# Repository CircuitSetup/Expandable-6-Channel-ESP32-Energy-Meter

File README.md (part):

# CircuitSetup Expandable 6 Channel ESP32 Energy Meter

The CircuitSetup Expandable 6 Channel ESP32 Energy Meter is a real-time power and energy monitor built around two ATM90E32AS metering ICs. The main board measures six current transformer channels and one voltage reference by default, and you can stack up to six add-on boards for a total of 42 current channels. It is a good fit for whole-home monitoring, subpanels, solar, large branch circuits, and multi-voltage or 3-phase projects.

The first AC-AC adapter powers the main board and provides the primary voltage reference. A second voltage can be measured on the main board, and stacked systems can monitor additional voltage references when the hardware is configured for it.

## Table of Contents

- [Quick Start: ESPHome via ESP Web Installer](#quick-start-esphome-via-esp-web-installer)
- [What You Will Need](#what-you-will-need)
- [Setting Up the Meter](#setting-up-the-meter)
- [Software Options](#software-options)
- [FAQ](#faq)
- [More Resources](#more-resources)

## Typical Uses

- North American split-phase 120V/240V 60Hz service: mains, solar, subpanels, and individual circuits
- Single-phase 230V/240V 50Hz or 60Hz systems with a suitable 9VAC or 12VAC AC-AC adapter
- 3-phase systems when each measured phase has the correct voltage reference

## Features

- 6 current channels on the main board
- Expandable to 42 current channels and up to 8 voltage references with add-on boards
- Built around two ATM90E32AS energy metering ICs
- Calculates active power, reactive power, apparent power, power factor, frequency, and temperature
- 16-bit measurement resolution
- 22 ohm burden resistors on each current channel
- Built-in buck converter to power the board and supported ESP32 dev boards
- SPI interface to the ESP32
- Energy pulse outputs, IRQ outputs, warning output, and zero-crossing signals are available on the board
- Typical metering IC accuracy is 0.1 percent with a 6000:1 dynamic range
- Current gain selection is available up to 4x

## Quick Start: ESPHome via ESP Web Installer

The fastest way to get the meter running is to flash ESPHome directly from the [CircuitSetup ESP Web Installer](https://circuitsetup.github.io/ESPWebInstaller/), connect it to your network, then adopt the device into Home Assistant.

### Flash Now With the Web Installer

1. Open the [CircuitSetup ESP Web Installer](https://circuitsetup.github.io/ESPWebInstaller/)
2. Under `6 Channel Meter`, choose:
   - the number of add-on boards
   - the connection type: `Wi-Fi`, `Ethernet (Lilygo)`, or `Ethernet (Waveshare)`
3. Choose the firmware version
4. Connect the ESP32 to your computer with a USB data cable
5. Click `Connect`, choose the correct serial port, and start the flash
6. If the board does not enter the bootloader automatically, hold the right or `IO0` button while the installer starts
7. If you flashed a Wi-Fi build, provision Wi-Fi after the flash
8. Once the device is online, adjust names, calibration values, and extra sensors as needed

The current Wi-Fi configs in this repo already include `captive_portal`, `esp32_improv`, and `improv_serial`, so the device can be provisioned before it is ever adopted into Home Assistant.

### Adopt Into Home Assistant/ESPHome Device Builder

If you want UI-based management, dashboard imports, OTA updates from Home Assistant, to change default meter/CT names, and do any other YAML editing, install ESPHome Device Builder after the first flash.

1. Open `Settings > Add-ons > Add-on Store`
2. Search for `ESPHome Device Builder`
3. Install it, then click `Start`
4. Click `Open Web UI`

The device should then appear in ESPHome Device Builder and in Home Assistant under `Settings > Devices & services`.

For package layout, local copies, calibration files, CS-pin changes, and advanced YAML examples, see [Software/ESPHome/](Software/ESPHome/).

## What You Will Need

### Current Transformers

You can use any mix of supported CTs as long as the secondary output does not exceed 720mV RMS or 33mA. CircuitSetup CTs with mA output work directly with the board and do not require cutting the burden resistor jumpers on the back.

- [SCT-006 20A/25mA Micro CT](https://circuitsetup.us/product/20a-25ma-micro-current-transformer-yhdc-sct-006-6mm/) - 6mm opening, 3.5mm plug
- [SCT-010 80A/26.6mA Mini CT](https://circuitsetup.us/product/80a-26-6ma-mini-current-transformer-yhdc-sct-010-10mm/) - 10mm opening, 3.5mm plug
- [SCT-013-000 100A/50mA CT](https://circuitsetup.us/product/100a-50ma-current-transformer-yhdc-sct-013/) - 13mm opening, 3.5mm plug
- [SCT-016 120A/40mA CT](https://circuitsetup.us/product/120a-40ma-current-transformer-yhdc-sct-016-with-3-5mm-jack-16mm-opening/) - 16mm opening, 3.5mm plug
- [SCT-024 200A/50mA CT](https://circuitsetup.us/product/200a-50ma-current-transformer-yhdc-sct-024-24mm/) - 24mm opening, 3.5mm plug
- Magnelab SCT-0750-100 and similar voltage-output CTs can also be used, but channels using CTs with built-in burden resistors require the matching jumper trace on the back of the board to be cut

### AC-AC Transformer

The meter requires an AC output transformer, not a DC wall adapter.

- North America: [Jameco Reliapro 120V to 9VAC](https://circuitsetup.us/product/jameco-ac-to-ac-wall-adapter-transformer-9-volt-1000ma-black-straight-2-5mm-female-plug/) or a similar 9VAC or 12VAC adapter with a 2.5mm center pin
- Europe and other 230V regions: use a native 230V to 9VAC or 12VAC AC-AC adapter rated for at least 500mA. [OpenEnergyMonitor keeps a useful list here](https://learn.openenergymonitor.org/electricity-monitoring/voltage-sensing/different-acac-power-adapters)

### ESP32

Supported and documented controller options:

- [NodeMCU 32s](https://circuitsetup.us/product/nodemcu-32s-esp32-esp-wroom-32-development-board/)
- Espressif ESP32-DevKitC-32E
- Espressif ESP32-DevKitC-VIE
- Boards with the same 19-pin-per-side pinout as the boards above
- Ethernet options for ESPHome only: [CircuitSetup ESP32-S3 Ethernet Adapter](https://circuitsetup.us/product/6-channel-energy-meter-ethernet-adapter/), [LilyGO T-ETH-Lite ESP32-S3](https://www.lilygo.cc/products/t-eth-lite?variant=43120880779445), or [Waveshare ESP32-S3 ETH](https://www.waveshare.com/esp32-s3-eth.htm?sku=28972)

Boards with different pin maps are not drop-in compatible just because they are "ESP32" boards. For example, ESP32-C6 dev boards use different pins and are not part of the documented support path for this repo.
If you are comparing boards visually, the documented dev boards are usually 19 pins per side, with `3V3` at the upper-left corner and `CLK` at the lower-right corner when installed correctly.

### Software

- [ESPHome](https://esphome.io/components/sensor/atm90e32/) and [Home Assistant](https://www.home-assistant.io/integrations/esphome/) - recommended for most new installs
- [EmonESP](Software/EmonESP/readme.md) and [EmonCMS](https://emoncms.org/) - good if you want EmonCMS or MQTT without Home Assistant
- [CircuitPython library](https://github.com/BitKnitting/CircuitSetup_CircuitPython)
- [MicroPython library](https://github.com/BitKnitting/CircuitSetup_micropython)

## Setting Up the Meter

### Plugging In the ESP32

The board is designed so the ESP32 dev board plugs directly into the meter.

Always insert the ESP32 with `3V3` in the upper-left corner of the meter. The lower pins are used to pass the voltage reference to add-on boards. Plugging the ESP32 into the lower row will likely short the board.

### Main Board SPI and Chip-Select Pins

The meter communicates with the ESP32 over SPI.

Main board SPI pins:

- `CLK` - GPIO18
- `MISO` - GPIO19
- `MOSI` - GPIO23
- `CS1` - GPIO5 for CT1-CT3 and Voltage 1
- `CS2` - GPIO4 for CT4-CT6 and Voltage 2

The 6-channel version of EmonESP in this repo is already set up with the main board pin defaults. Current ESPHome configs for the main board and add-on boards are in [Software/ESPHome](Software/ESPHome).

### Add-On Boards

Each add-on board adds six more CT channels. Up to six add-on boards can be stacked on the main board.

Each add-on board has two CS jumper banks:

- `CS` for CT1-CT3 on that add-on board
- `CS2` for CT4-CT6 on that add-on board

Only choose one pin per bank. The default jumper positions used by the installer and repo configs are:

| Add-on board | `CS` for CT1-CT3 | `CS2` for CT4-CT6 |
| --- | --- | --- |
| 1st add-on | GPIO0 | GPIO16 |
| 2nd add-on | GPIO27 | GPIO17 |
| 3rd add-on | GPIO2 | GPIO21 |
| 4th add-on | GPIO13 | GPIO22 |
| 5th add-on | GPIO14 | GPIO25 |
| 6th add-on | GPIO15 | GPIO26 |

GPIO2 can interfere with programming on some ESP32 boards. If you temporarily cannot flash the ESP32 while that jumper is connected, disconnect that add-on board or move the jumper while programming, then restore the expected setting.

If you change jumper positions from the defaults, update the matching `cs_pin` values in your ESPHome config. See [Software/ESPHome/README.md](Software/ESPHome/README.md) for examples.

### CT Compatibility, Burden Resistors, and `JP1-JP6`

Each current channel on the board has an onboard burden resistor. That is correct for CircuitSetup CTs with mA output.

Only cut the matching rear jumper trace for a CT channel if that CT already has its own burden resistor, which is usually the case for voltage-output CTs such as 1V-output models.

In practice:

- CircuitSetup SCT-006, SCT-010, SCT-013-000, SCT-016, and SCT-024 CTs do not require cutting `JP1-JP6`
- 1V-output CTs such as SCT-013-030 or SCT-013-050 do require cutting the matching jumper trace for the channel they are connected to
- If you are mixing CT types, only cut the jumper traces for the specific channels using CTs with built-in burden resistors

### Common Calibration Starting Values

Each current channel can use its own calibration value. In the current ESPHome configs that means setting `current_cal_ct1`, `current_cal_ct2`, and so on for the main board, plus the add-on board calibration variables where needed.

Common starting values:

| Sensor | Calibration value |
| --- | --- |
| SCT-006 20A/25mA | `11143` |
| SCT-013-030 30A/1V | `8650` |
| SCT-013-050 50A/1V | `15420` |
| SCT-010 50A/16.6mA | `41334` |
| SCT-010 80A/26.6mA | `41660` |
| SCT-013-000 100A/50mA | `27518` |
| SCT-016 120A/40mA | `41787` |
| SCT-024 200A/100mA | `27518` |
| SCT-024 200A/50mA | `55036` |
| Jameco 9VAC transformer | `7305` |

These are good starting points, not guaranteed final values. If you want tighter accuracy, use the ESPHome semi-automatic calibration workflow described below.

### Measuring More Than 65A on One Channel

The ATM90E32 current register tops out at `65.535A` before scaling. If you expect to measure more than that on one channel, divide the CT calibration value and multiply the reported current and power in software. Current examples are already documented in [Software/ESPHome/README.md](Software/ESPHome/README.md) and shown in [Software/ESPHome/6chan_energy_meter_main_board.yaml](Software/ESPHome/6chan_energy_meter_main_board.yaml).

For 200A service this usually means you are monitoring a larger CT but scaling it in software so the meter stays within range.

### Power Calculations and Board Revisions

The board uses voltage references to calculate power, power factor, and the other metering values.

- v1.1 used one voltage channel per ATM90E32 by default, so some power calculations had to be done in software unless registers were remapped
- v1.2 and v1.3 added `JP8-JP11` so voltage channels could be tied together. Most v1.3 boards shipped with those connections already joined
- v1.4 and later removed `JP8-JP11` and route those voltage channels internally on the PCB

### Measuring Dual-Pole 240V Circuits on Split-Phase Service

For split-phase systems, a 240V load has two hot legs. There are three practical ways to measure it:

1. Measure one hot leg with one CT and double the current and power in software. This uses the fewest channels but is the least accurate.
2. Measure each hot leg with its own CT. This is the most flexible option.
3. If the wiring layout allows it and the CT opening is large enough, pass both hot legs through a single CT in opposite directions.

If a CT is not in phase with its voltage reference, current and power will read negative. On split-phase systems that usually means the CT is flipped around the wrong conductor.

### Measuring a Second Voltage

The `VA2` pads next to the power jack on the main board, and the `VA2` pads on add-on boards, let you measure a second voltage reference.

To do that:

1. Cut `JP12` and `JP13` on v1.3 and newer boards, or `JP7` on older revisions
2. Use a second AC-AC transformer, ideally the same model as the primary one
3. Connect that second transformer to the opposite phase you want to reference
4. Add a suitable connector or pigtail to the `VA2+` and `VA2-` pads

When those voltage jumpers are cut:

- CT1-CT3 stay referenced to the primary voltage
- CT4-CT6 use the `VA2` voltage reference

That means CT4-CT6 should measure circuits on the same phase as `VA2`, or the CT direction must be reversed so the current is in phase with the voltage reference.

On add-on boards, the primary voltage normally comes from the main board. If you wire a separate `VA2` voltage reference on an add-on board, that secondary voltage is used for CT4-CT6 on that add-on board.

### Measuring 3-Phase Power

For accurate 3-phase power metering you need a matching voltage reference for each measured phase.

The cleanest 3-phase setup is:

- one main board, v1.4 or newer
- one add-on board
- three AC-AC transformers, one per phase
- headers or connectors installed on the `VA2` pads as needed
- `JP12` and `JP13` cut on the boards where separate voltage references are being used

The first transformer connected to the main board also powers the electronics and ESP32, so it should provide at least 500mA.

With that hardware:

- main board CT1-CT3 can reference phase 1
- main board CT4-CT6 can reference phase 2
- add-on board CT1-CT6 can reference phase 3, depending on how you feed voltage to that board

An alternate 3-phase approach is to use two add-on boards and feed a separate transformer into each add-on board. In that setup, the bottom `VA-` and `VA+` feed from the main board is no longer used for those add-ons, and you wire the new transformer to the `VA2` pads on each add-on instead.

If a CT is tied to a different phase than its voltage reference, active power and power factor will be wrong even if current itself looks reasonable.

## Software Options

### ESPHome and Home Assistant

ESPHome is still the recommended software path. If you just want to get firmware onto the meter, use the quick-start section above. The rest of this section covers what the maintained ESPHome configs already include after the device is flashed.

Useful references:

- [Getting Started with ESPHome and Home Assistant](https://esphome.io/guides/getting_started_hassio/)
- [ESPHome ATM90E32 docs](https://esphome.io/components/sensor/atm90e32/)

### What the Default ESPHome Config Already Includes

The current repo configs are built for the current ESPHome workflow, not the older legacy setup:

- `dashboard_import` so the device can be adopted into ESPHome Device Builder
- `name_add_mac_suffix: true` so multiple identical meters do not collide on the network
- `ota: - platform: esphome` for current OTA updates
- `captive_portal`, `esp32_improv`, and `improv_serial` on Wi-Fi builds for provisioning
- `time: - platform: homeassistant` in the shared packages used by the standard configs

After the first flash:

- Wi-Fi builds can be provisioned from the browser, via Improv, or through the fallback captive portal if the device is not yet on your network
- Ethernet builds come up on your wired network once flashed and connected
- The device should appear in ESPHome Device Builder and in Home Assistant under `Settings > Devices & services`
- You can edit the imported YAML inside ESPHome Device Builder, or copy the files locally from [Software/ESPHome](Software/ESPHome) if you prefer to manage everything yourself

If you want the maintained package-based configs, start from the files in [Software/ESPHome](Software/ESPHome). If you want more control, use [Software/ESPHome/README.md](Software/ESPHome/README.md) as the advanced reference for package layout, calibration files, CS-pin changes, and example configs.

### ESPHome Calibration

Default calibration values are usually good enough to get started, but calibration is strongly recommended if you are using custom CTs, a different AC-AC transformer, longer CT leads, or if you want especially accurate readings.

On the main board, calibration is done through two separate ATM90E32 chips, not one 6-channel block. `main_meter_id1` / `Meter 1-3` handles CTs `1-3`, and `main_meter_id2` / `Meter 4-6` handles CTs `4-6`. Each `Run ... Calibration` button in Home Assistant acts on only one of those chips, so calibrate CTs `1-3` and CTs `4-6` separately.

In the CircuitSetup YAML, the normal starting points are `current_cal_ct1` through `current_cal_ct6`, plus `voltage_cal1` and `voltage_cal2` in the top-level config file you flashed or imported from [Software/ESPHome](Software/ESPHome). Under the hood, those map to ESPHome's `gain_ct` and `gain_voltage` values for each ATM90E32 phase. [Software/ESPHome/calibration/6chan_main_calibration.yaml](Software/ESPHome/calibration/6chan_main_calibration.yaml) adds the Home Assistant calibration buttons and the runtime reference number entities. [Software/ESPHome/calibration/6chan_main_offset_calibrations.yaml](Software/ESPHome/calibration/6chan_main_offset_calibrations.yaml) is where copied offset values can be persisted in YAML.

To use the semi-automatic calibration workflow, make sure `offset_calibration` and `gain_calibration` are set to `"true"` and that the calibration package is included. After the meter is adopted into Home Assistant, open the meter device page. There you will see:

- `${main_meter_name1} Ref V 1` and `CT1 Ref Current` through `CT3 Ref Current` for the first ATM90E32
- `${main_meter_name2} Ref V 2` and `CT4 Ref Current` through `CT6 Ref Current` for the second ATM90E32
- `Run ... Offset Cal`, `Run ... Power Offset Cal`, `Run ... Gain Cal`, and matching `Clear ...` buttons for each chip

If you renamed the meter groups in YAML, the button labels will follow those names instead of the default `Meter 1-3` and `Meter 4-6`.

In practice:

- gain calibration fixes scaling when the meter reads high or low under a known load
- offset calibration fixes false zero-level readings when current or voltage should be at or very near zero
- power-offset calibration fixes false power readings when voltage is present but CT current is zero

Recommended workflow:

1. Start with the closest known values for your CTs and AC transformer by setting `current_cal_ct1` through `current_cal_ct6` and `voltage_cal1`/`voltage_cal2` to the nearest matching starting values.
2. Open the meter device page in Home Assistant and choose which ATM90E32 you are calibrating: `Meter 1-3` for CTs `1-3`, or `Meter 4-6` for CTs `4-6`. For that chip, phase A/B/C in the ESPHome logs correspond to CT1/CT2/CT3 or CT4/CT5/CT6 respectively.
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
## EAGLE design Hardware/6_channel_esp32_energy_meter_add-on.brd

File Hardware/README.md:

## Expandable 6 Channel Energy Meter Change Log
**3/2/2020 - v1.4 rev1**
- Changed micro-hdmi connector to through-hole
- Changed spacing on VA2+/VA2- (voltage 2 connection) to 3.5mm to allow for standard screw connectors

**12/16/2019 – v1.4**
- Added optional micro-hdmi connection to connect the current transformer remote board. This allows for all 6 current transformer connections to connect to a remote pcb, which then connects to the main board via 1 micro-hdmi cable. Instead of 6 wires coming out of the meter, there can now be 1.
- Added current transformer remote pcb
- Removed JP8-JP11 and connected all voltage channels together for each ATM90E32

**10/15/2019 – v1.3 rev1**
- Added voltage divider on ground for voltage channel 2
- Added JP12 & JP13 to disconnect voltage channel 1 from 2

**10/1/2019 – v1.3**
- Added voltage divider on ground for voltage channel 1
- Added 20k pullup for voltage channel 1
- Changed all voltage dividers to 20k and 1k so voltage input from a 12v AC transformer is around 650mV - this allows more voltage in than previous versions, lowering the voltage calibration
- Removed C37

**8/1/2019 – v1.2**
- Added C37 to connect neutral and DC ground
- Added solder jumpers JP8JP12 to connect all voltage channel inputs together

**6/1/2019 – v1.1**
- Initial public release

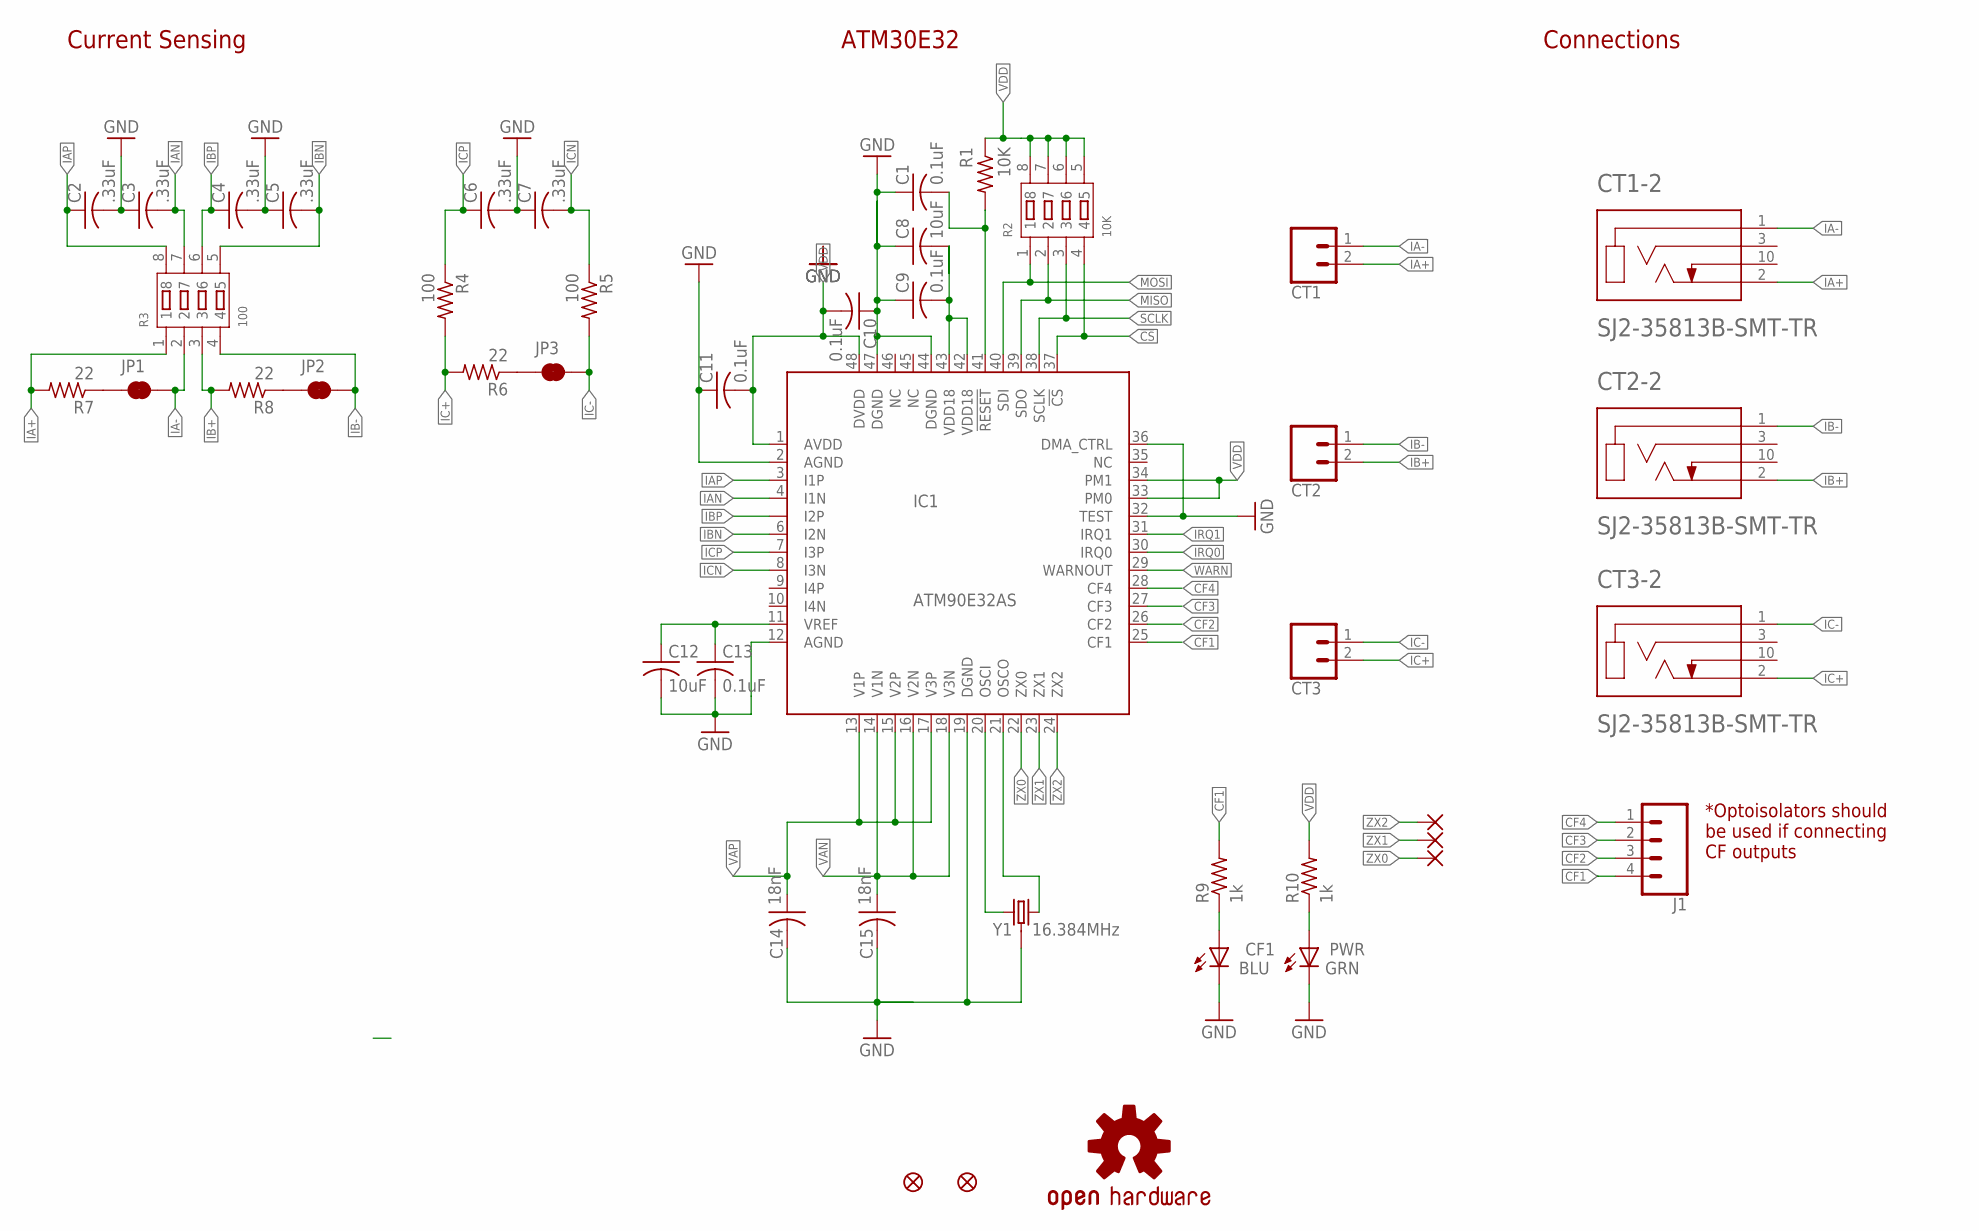
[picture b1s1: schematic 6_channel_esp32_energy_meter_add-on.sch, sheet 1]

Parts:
C1, C9, C10, C11, C13: 0.1uF; C0603
C2, C3, C4, C5, C6, C7: .33uF; C0603
C8, C12: 10uF; C0603
C14, C15: 18nF; C0603
CF1: BLU; CHIPLED_0603
CT1, CT2, CT3: CONN_023.5MM; SCREWTERMINAL-3.5MM-2
CT1-2, CT2-2, CT3-2: SJ2-35813B-SMT-TR; CUI_SJ2-35813B-SMT-TR
FD1, FD2: FIDUCIALUFIDUCIAL; FIDUCIAL-MICRO
IC1: ATM90E32AS; QFP50P900X900X120-48
J1: CONN_04; 1X04
JP1, JP2, JP3: JUMPER-SMT_2_NC_TRACE_SILK; SMT-JUMPER_2_NC_TRACE_SILK
LOGO1: OSHW-LOGOS; OSHW-LOGO-S
PWR: GRN; CHIPLED_0603
R1: 10K; R0603
R2: 10K; RA1206-8
R3: 100; RA1206-8
R4, R5: 100; R0603
R6, R7, R8: 22; R0603
R9, R10: 1k; R0603
Y1: 16.384MHz; CRYSTAL-SMD-3.2X2.5MM
ZX0, ZX1, ZX2: WIREPADSMD1,27-254; SMD1,27-2,54

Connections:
!CS: IC1.37 (!CS), R2.4; also elsewhere on the board
!RESET: C1.2, IC1.41 (!RESET), R1.2
CF1: IC1.25 (CF1), J1.4, R9.2
CF2: IC1.26 (CF2), J1.3
CF3: IC1.27 (CF3), J1.2
CF4: IC1.28 (CF4), J1.1
GND: C1.1, C2.2, C3.1, C4.2, C5.1, C6.2, C7.1, C8.1, C9.1, C10.1, C11.1, C12.2, C13.2, C14.2, C15.2, CF1.C, IC1.2 (AGND), IC1.12 (AGND), IC1.19 (DGND), IC1.32 (TEST), IC1.36 (DMA_CTRL), IC1.44 (DGND), IC1.47 (DGND), PWR.C, Y1.2 (3), Y1.4 (3); also elsewhere on the board
IA+: CT1.2, CT1-2.2 (TIP), R3.1, R7.2; also elsewhere on the board
IA-: CT1.1, CT1-2.1 (SLEEVE), JP1.2, R3.2; also elsewhere on the board
IAN: C3.2, IC1.4 (I1N), R3.7
IAP: C2.1, IC1.3 (I1P), R3.8
IB+: CT2.2, CT2-2.2 (TIP), R3.3, R8.2; also elsewhere on the board
IB-: CT2.1, CT2-2.1 (SLEEVE), JP2.2, R3.4; also elsewhere on the board
IBN: C5.2, IC1.6 (I2N), R3.5
IBP: C4.1, IC1.5 (I2P), R3.6
IC+: CT3.2, CT3-2.2 (TIP), R4.2, R6.2; also elsewhere on the board
IC-: CT3.1, CT3-2.1 (SLEEVE), JP3.2, R5.2; also elsewhere on the board
ICN: C7.2, IC1.8 (I3N), R5.1
ICP: C6.1, IC1.7 (I3P), R4.1
IRQ0: IC1.30 (IRQ0); also elsewhere on the board
IRQ1: IC1.31 (IRQ1); also elsewhere on the board
MISO: IC1.39 (SDO), R2.2; also elsewhere on the board
MOSI: IC1.40 (SDI), R2.1; also elsewhere on the board
unnamed: JP1.1, R7.1
unnamed: JP2.1, R8.1
unnamed: CF1.A, R9.1
unnamed: JP3.1, R6.1
unnamed: PWR.A, R10.1
OSCI: IC1.20 (OSCI), Y1.1
OSCO: IC1.21 (OSCO), Y1.3 (2)
SCLK: IC1.38 (SCLK), R2.3; also elsewhere on the board
VAN: C15.1, IC1.14 (V1N), IC1.16 (V2N), IC1.18 (V3N); also elsewhere on the board
VAP: C14.1, IC1.13 (V1P), IC1.15 (V2P), IC1.17 (V3P); also elsewhere on the board
VDD: C10.2, C11.2, IC1.1 (AVDD), IC1.33 (PM0), IC1.34 (PM1), IC1.48 (DVDD), R1.1, R2.5, R2.6, R2.7, R2.8, R10.2; also elsewhere on the board
VDD18: C8.2, C9.2, IC1.42 (VDD18), IC1.43 (VDD18)
VREF: C12.1, C13.1, IC1.11 (VREF)
WARN: IC1.29 (WARNOUT); also elsewhere on the board
ZX0: IC1.22 (ZX0), ZX0.1
ZX1: IC1.23 (ZX1), ZX1.1
ZX2: IC1.24 (ZX2), ZX2.1

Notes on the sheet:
ATM30E32
Connections
*Optoisolators should be used if connecting CF outputs
Current Sensing

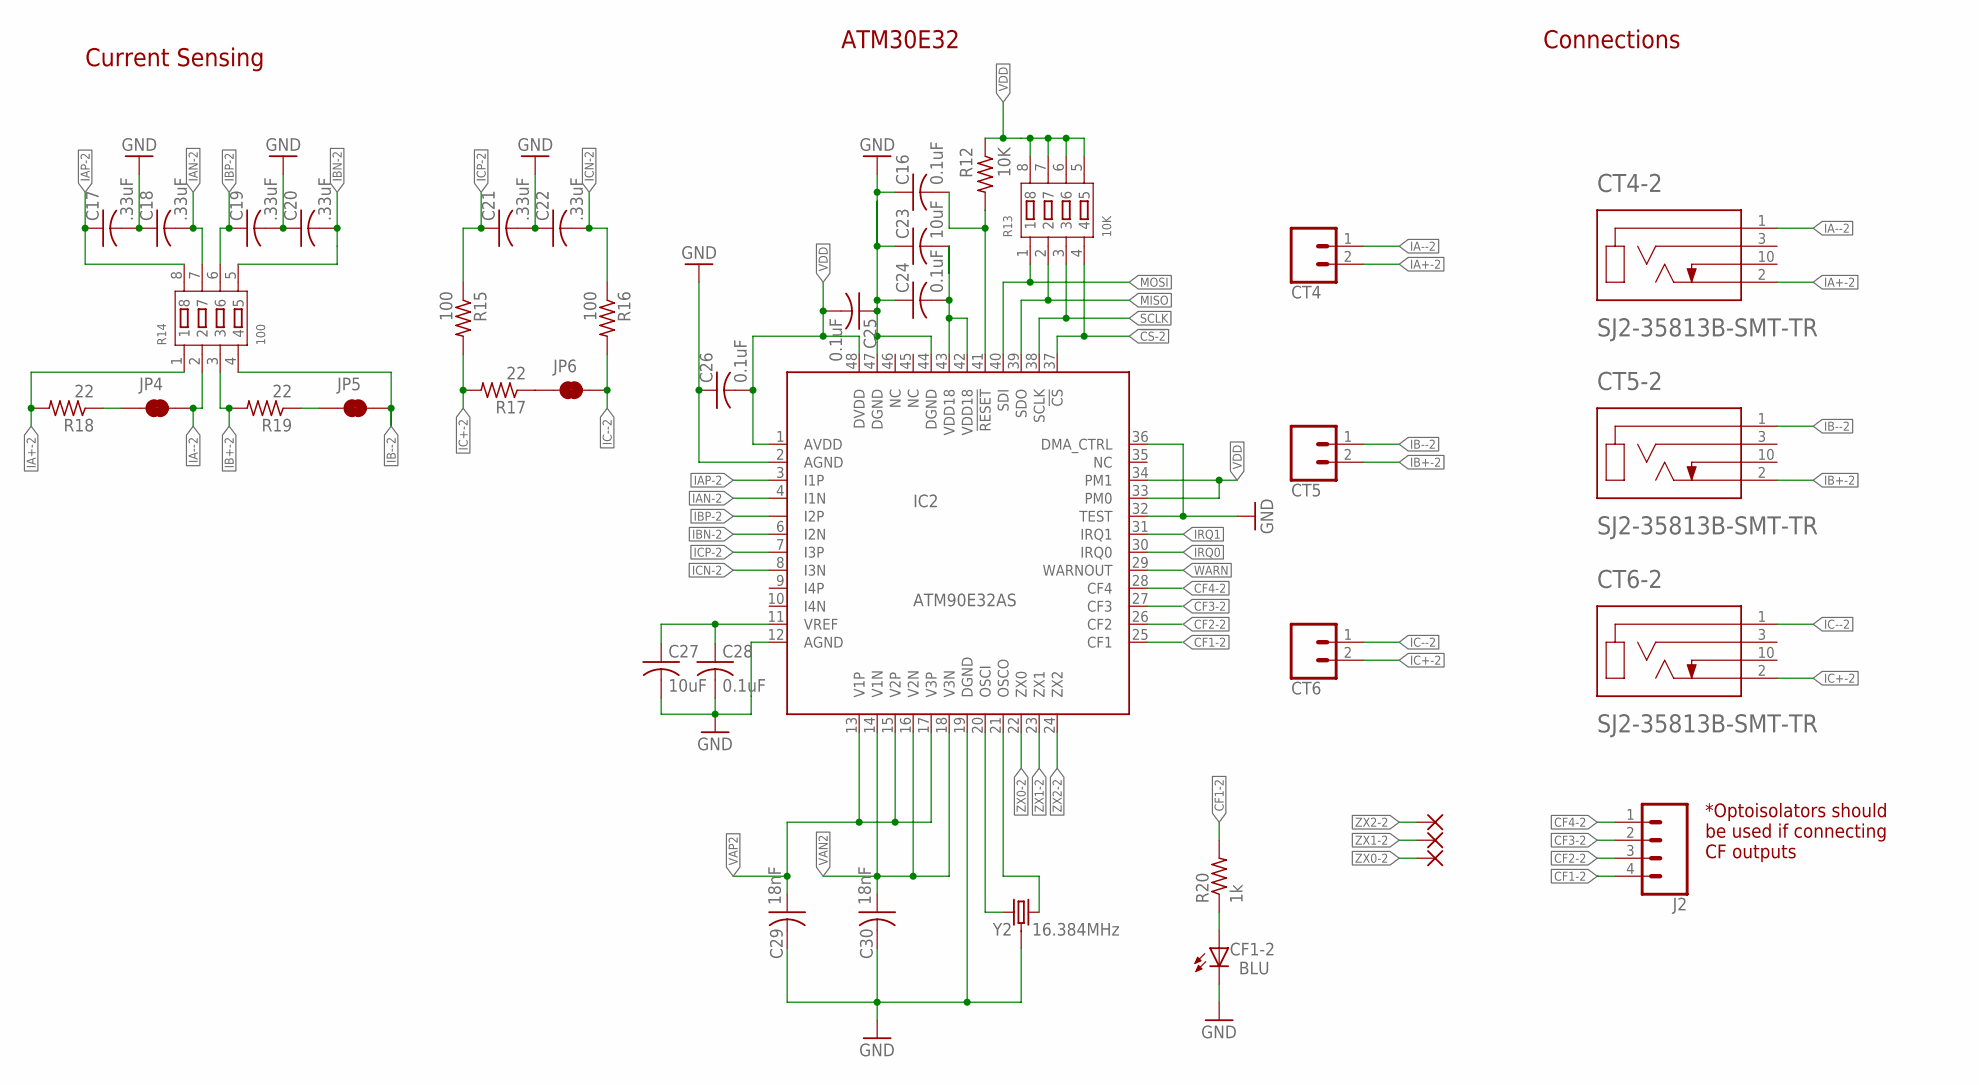
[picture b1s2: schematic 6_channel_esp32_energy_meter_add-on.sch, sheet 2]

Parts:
C16, C24, C25, C26, C28: 0.1uF; C0603
C17, C18, C19, C20, C21, C22: .33uF; C0603
C23, C27: 10uF; C0603
C29, C30: 18nF; C0603
CF1-2: BLU; CHIPLED_0603
CT4, CT5, CT6: CONN_023.5MM; SCREWTERMINAL-3.5MM-2
CT4-2, CT5-2, CT6-2: SJ2-35813B-SMT-TR; CUI_SJ2-35813B-SMT-TR
IC2: ATM90E32AS; QFP50P900X900X120-48
J2: CONN_04; 1X04
JP4, JP5, JP6: JUMPER-SMT_2_NC_TRACE_SILK; SMT-JUMPER_2_NC_TRACE_SILK
R12: 10K; R0603
R13: 10K; RA1206-8
R14: 100; RA1206-8
R15, R16: 100; R0603
R17, R18, R19: 22; R0603
R20: 1k; R0603
Y2: 16.384MHz; CRYSTAL-SMD-3.2X2.5MM
ZX0-2, ZX1-2, ZX2-2: WIREPADSMD1,27-254; SMD1,27-2,54

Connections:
!CS-2: IC2.37 (!CS), R13.4; also elsewhere on the board
!RESET2: C16.2, IC2.41 (!RESET), R12.2
CF1-2: IC2.25 (CF1), J2.4, R20.2
CF2-2: IC2.26 (CF2), J2.3
CF3-2: IC2.27 (CF3), J2.2
CF4-2: IC2.28 (CF4), J2.1
GND: C16.1, C17.2, C18.1, C19.2, C20.1, C21.2, C22.1, C23.1, C24.1, C25.1, C26.1, C27.2, C28.2, C29.2, C30.2, CF1-2.C, IC2.2 (AGND), IC2.12 (AGND), IC2.19 (DGND), IC2.32 (TEST), IC2.36 (DMA_CTRL), IC2.44 (DGND), IC2.47 (DGND), Y2.2 (3), Y2.4 (3); also elsewhere on the board
IA+-2: CT4.2, CT4-2.2 (TIP), R14.1, R18.2; also elsewhere on the board
IA--2: CT4.1, CT4-2.1 (SLEEVE), JP4.2, R14.2; also elsewhere on the board
IAN-2: C18.2, IC2.4 (I1N), R14.7
IAP-2: C17.1, IC2.3 (I1P), R14.8
IB+-2: CT5.2, CT5-2.2 (TIP), R14.3, R19.2; also elsewhere on the board
IB--2: CT5.1, CT5-2.1 (SLEEVE), JP5.2, R14.4; also elsewhere on the board
IBN-2: C20.2, IC2.6 (I2N), R14.5
IBP-2: C19.1, IC2.5 (I2P), R14.6
IC+-2: CT6.2, CT6-2.2 (TIP), R15.2, R17.2; also elsewhere on the board
IC--2: CT6.1, CT6-2.1 (SLEEVE), JP6.2, R16.2; also elsewhere on the board
ICN-2: C22.2, IC2.8 (I3N), R16.1
ICP-2: C21.1, IC2.7 (I3P), R15.1
IRQ0: IC2.30 (IRQ0); also elsewhere on the board
IRQ1: IC2.31 (IRQ1); also elsewhere on the board
MISO: IC2.39 (SDO), R13.2; also elsewhere on the board
MOSI: IC2.40 (SDI), R13.1; also elsewhere on the board
unnamed: JP4.1, R18.1
unnamed: JP5.1, R19.1
unnamed: JP6.1, R17.1
unnamed: CF1-2.A, R20.1
OSCI2: IC2.20 (OSCI), Y2.1
OSCO2: IC2.21 (OSCO), Y2.3 (2)
SCLK: IC2.38 (SCLK), R13.3; also elsewhere on the board
VAN2: C30.1, IC2.14 (V1N), IC2.16 (V2N), IC2.18 (V3N); also elsewhere on the board
VAP2: C29.1, IC2.13 (V1P), IC2.15 (V2P), IC2.17 (V3P); also elsewhere on the board
VDD: C25.2, C26.2, IC2.1 (AVDD), IC2.33 (PM0), IC2.34 (PM1), IC2.48 (DVDD), R12.1, R13.5, R13.6, R13.7, R13.8; also elsewhere on the board
VDD2: C23.2, C24.2, IC2.42 (VDD18), IC2.43 (VDD18)
VREF2: C27.1, C28.1, IC2.11 (VREF)
WARN: IC2.29 (WARNOUT); also elsewhere on the board
ZX0-2: IC2.22 (ZX0), ZX0-2.1
ZX1-2: IC2.23 (ZX1), ZX1-2.1
ZX2-2: IC2.24 (ZX2), ZX2-2.1

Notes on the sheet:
ATM30E32
Connections
*Optoisolators should be used if connecting CF outputs
Current Sensing

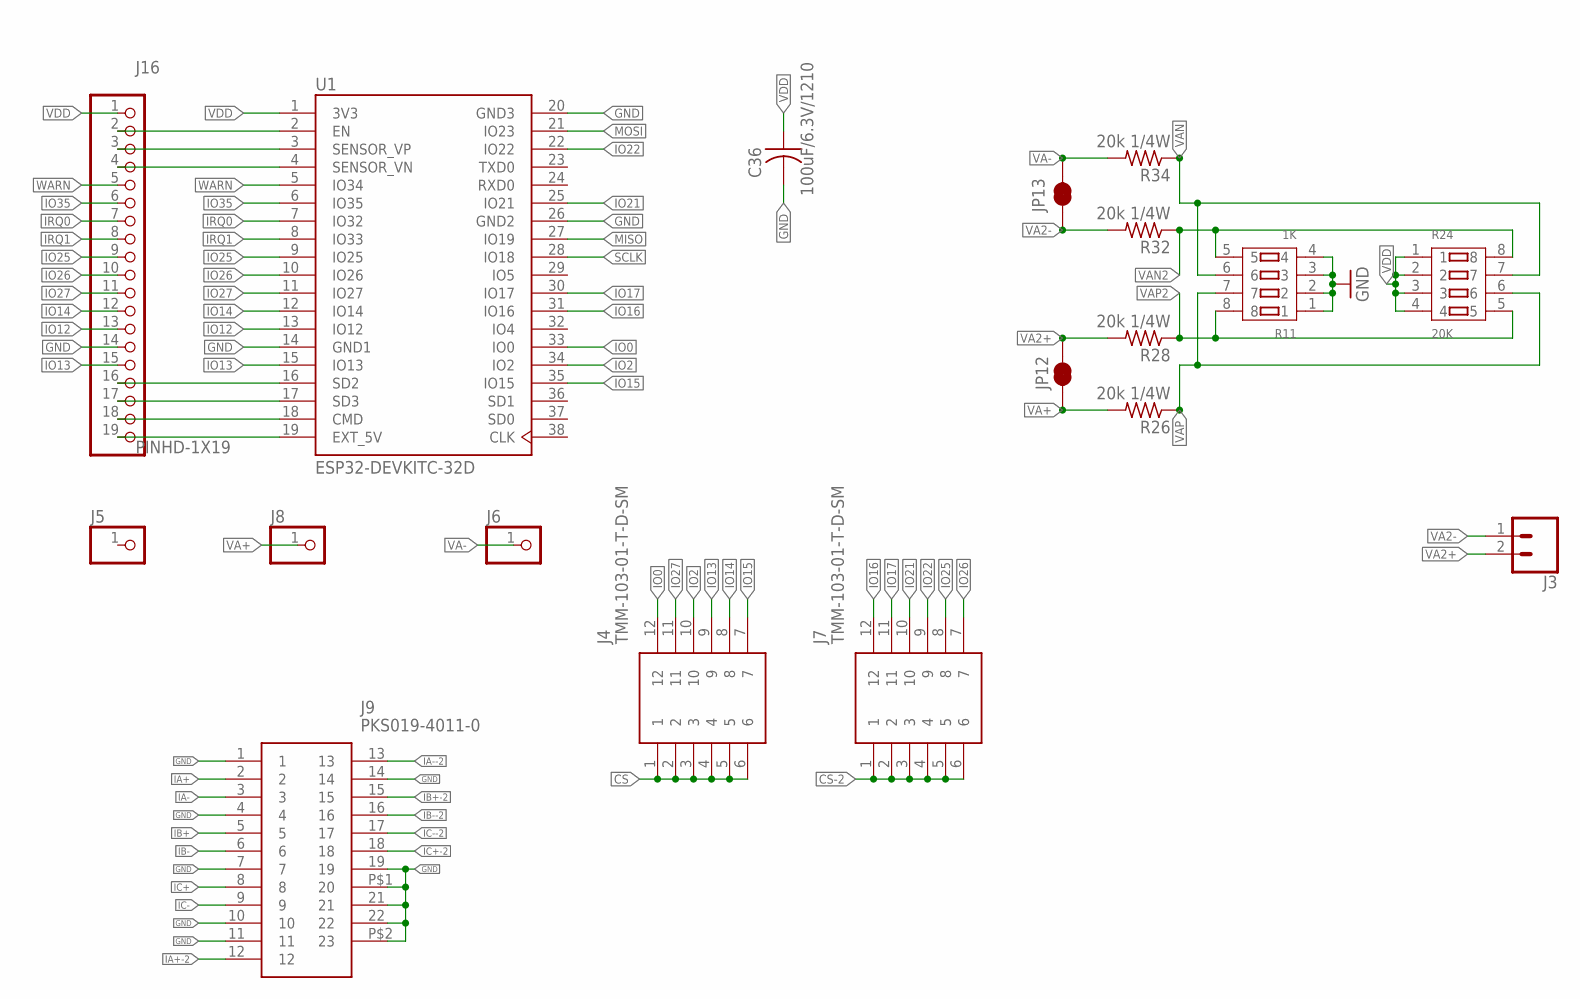
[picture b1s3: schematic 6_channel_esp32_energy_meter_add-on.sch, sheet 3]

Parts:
C36: 100uF/6.3V/1210; C1210
J3: CONN_023.5MM; SCREWTERMINAL-3.5MM-2
J4, J7: TMM-103-01-T-D-SM; SOP200P706X597-12N
J5, J6, J8: PINHD1X1-SM1X01_SM; 1X01-SM
J9: PKS019-4011-0; PKS01940110
J16: PINHD-1X19; 1X19
JP12, JP13: JUMPER-SMT_2_NC_TRACE_SILK; SMT-JUMPER_2_NC_TRACE_SILK
R11: 1K; RA1206-8
R24: 20K; RA1206-8
R26, R28, R32, R34: 20k 1/4W; R0603
U1: ESP32-DEVKITC-32D; MODULE_ESP32-DEVKITC-32D

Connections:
!CS: J4.1, J4.2, J4.3, J4.4, J4.5, J4.6; also elsewhere on the board
!CS-2: J7.1, J7.2, J7.3, J7.4, J7.5, J7.6; also elsewhere on the board
GND: C36.2, J9.1, J9.4, J9.7, J9.10, J9.11, J9.14, J9.19, J9.21, J9.22, J9.P$1 (20), J9.P$2 (23), J16.14, R11.1, R11.2, R11.3, R11.4, U1.14 (GND1), U1.20 (GND3), U1.26 (GND2); also elsewhere on the board
IA+: J9.2; also elsewhere on the board
IA+-2: J9.12; also elsewhere on the board
IA-: J9.3; also elsewhere on the board
IA--2: J9.13; also elsewhere on the board
IB+: J9.5; also elsewhere on the board
IB+-2: J9.15; also elsewhere on the board
IB-: J9.6; also elsewhere on the board
IB--2: J9.16; also elsewhere on the board
IC+: J9.8; also elsewhere on the board
IC+-2: J9.18; also elsewhere on the board
IC-: J9.9; also elsewhere on the board
IC--2: J9.17; also elsewhere on the board
IO0: J4.12, U1.33 (IO0)
IO2: J4.10, U1.34 (IO2)
IO12: J16.13, U1.13 (IO12)
IO13: J4.9, J16.15, U1.15 (IO13)
IO14: J4.8, J16.12, U1.12 (IO14)
IO15: J4.7, U1.35 (IO15)
IO16: J7.12, U1.31 (IO16)
IO17: J7.11, U1.30 (IO17)
IO21: J7.10, U1.25 (IO21)
IO22: J7.9, U1.22 (IO22)
IO25: J7.8, J16.9, U1.9 (IO25)
IO26: J7.7, J16.10, U1.10 (IO26)
IO27: J4.11, J16.11, U1.11 (IO27)
IO35: J16.6, U1.6 (IO35)
IRQ0: J16.7, U1.7 (IO32); also elsewhere on the board
IRQ1: J16.8, U1.8 (IO33); also elsewhere on the board
MISO: U1.27 (IO19); also elsewhere on the board
MOSI: U1.21 (IO23); also elsewhere on the board
unnamed: J16.2, U1.2 (EN)
unnamed: J16.3, U1.3 (SENSOR_VP)
unnamed: J16.4, U1.4 (SENSOR_VN)
unnamed: J16.16, U1.16 (SD2)
unnamed: J16.17, U1.17 (SD3)
unnamed: J16.18, U1.18 (CMD)
unnamed: J16.19, U1.19 (EXT_5V)
SCLK: U1.28 (IO18); also elsewhere on the board
VA2+: J3.2, JP12.1, R28.2
VA2-: J3.1, JP13.1, R32.2
VA+: J8.1, JP12.2, R26.2
VA-: J6.1, JP13.2, R34.2
VAN: R11.6, R24.7, R34.1; also elsewhere on the board
VAN2: R11.5, R24.8, R32.1; also elsewhere on the board
VAP: R11.7, R24.6, R26.1; also elsewhere on the board
VAP2: R11.8, R24.5, R28.1; also elsewhere on the board
VDD: C36.1, J16.1, R24.1, R24.2, R24.3, R24.4, U1.1 (3V3); also elsewhere on the board
WARN: J16.5, U1.5 (IO34); also elsewhere on the board

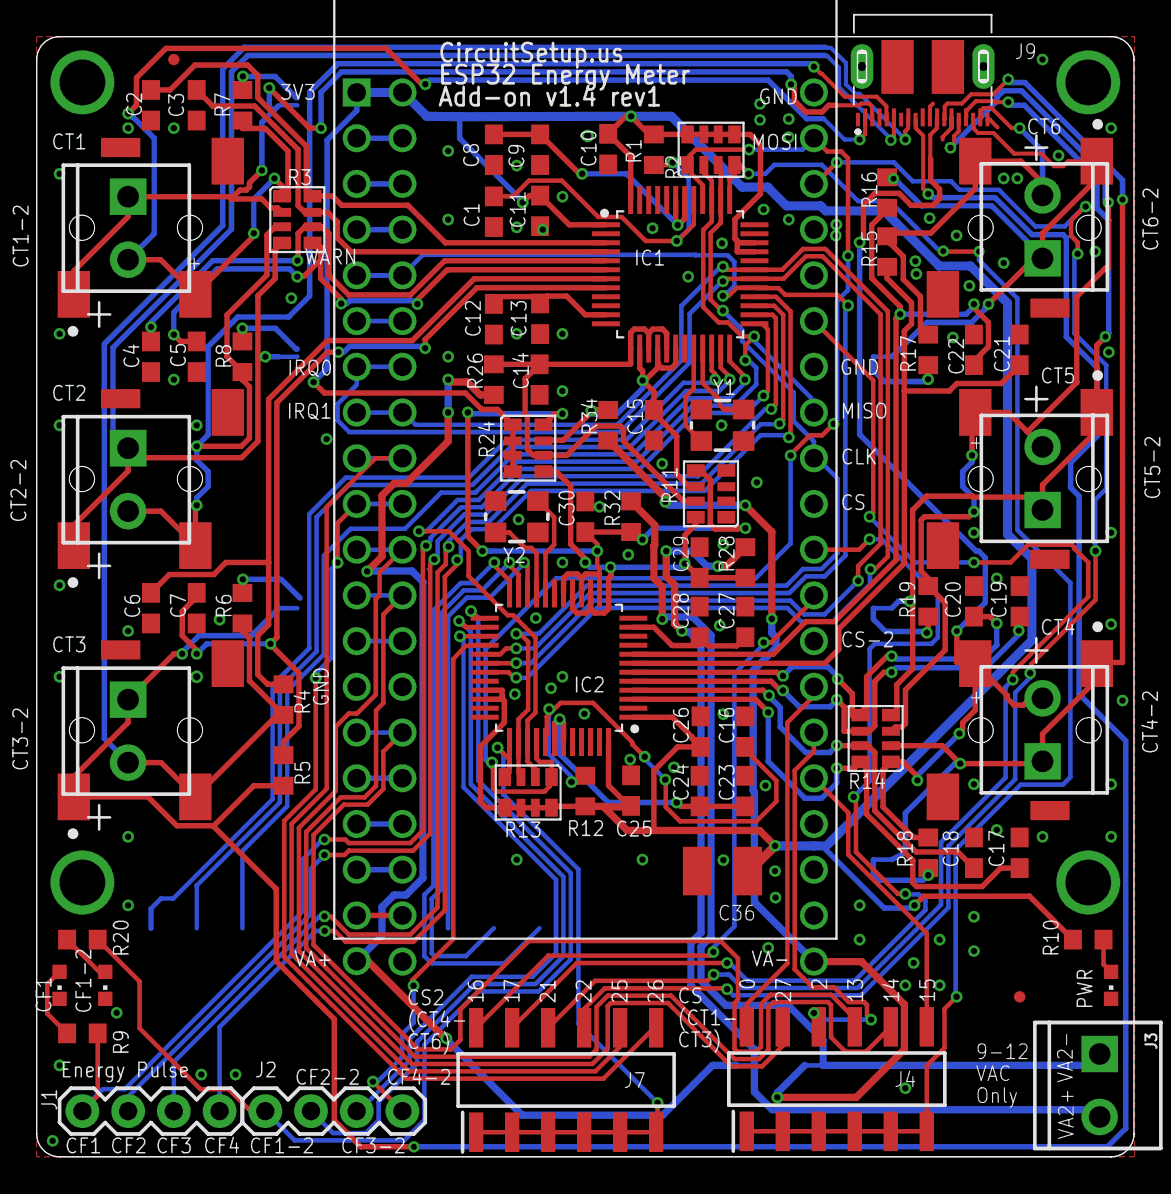
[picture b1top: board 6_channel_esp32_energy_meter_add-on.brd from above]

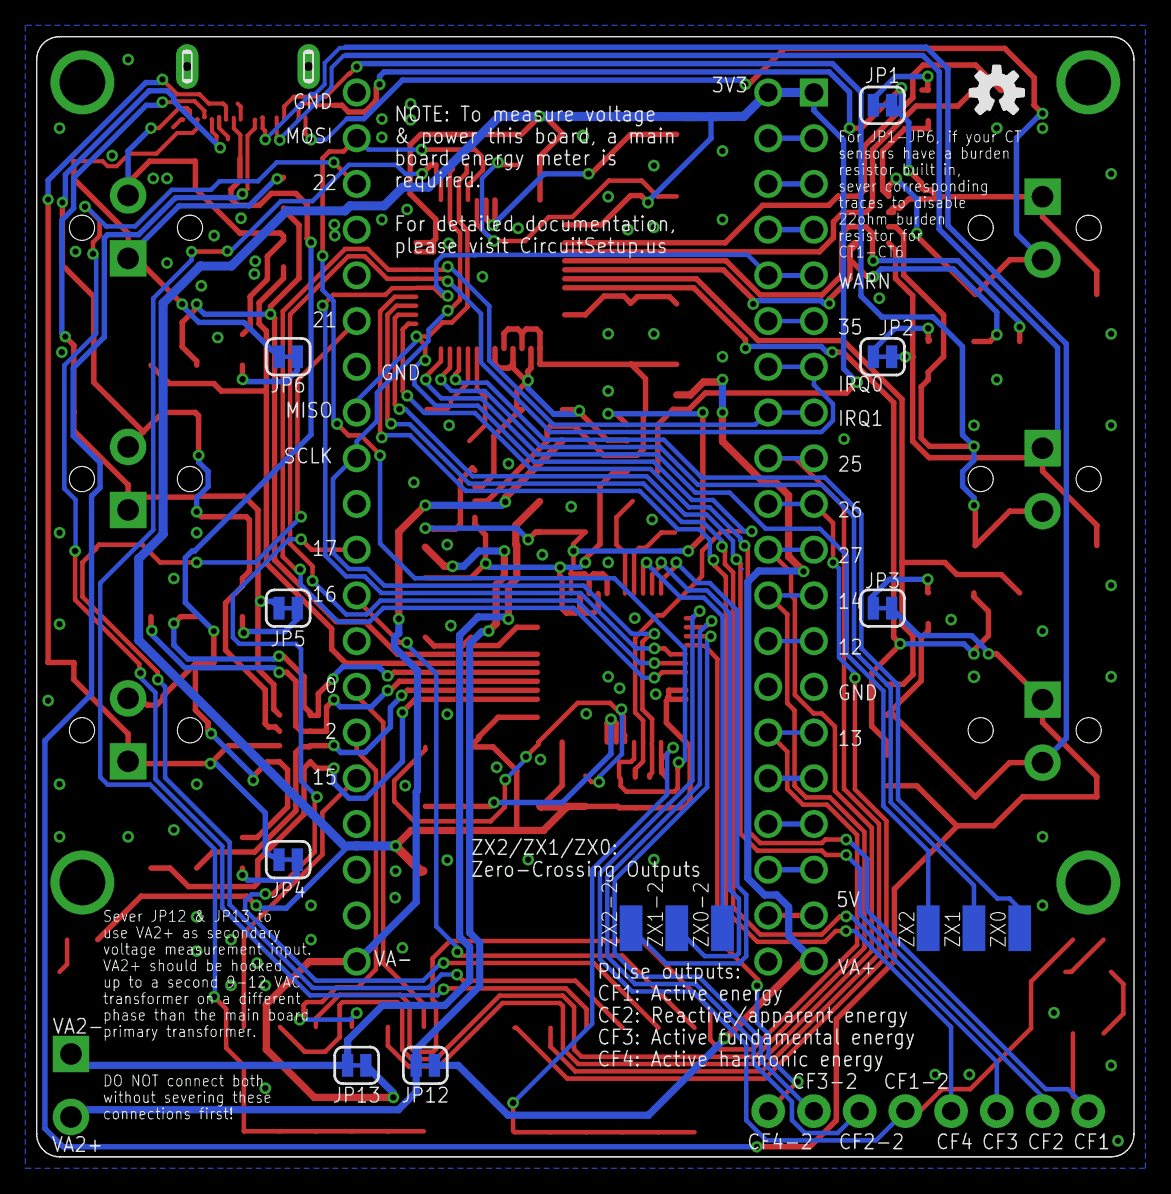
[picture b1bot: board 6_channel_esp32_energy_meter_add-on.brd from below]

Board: 2 copper layers, 61.0 x 62.2 mm, 103 parts (15 on the bottom side), 96 nets.

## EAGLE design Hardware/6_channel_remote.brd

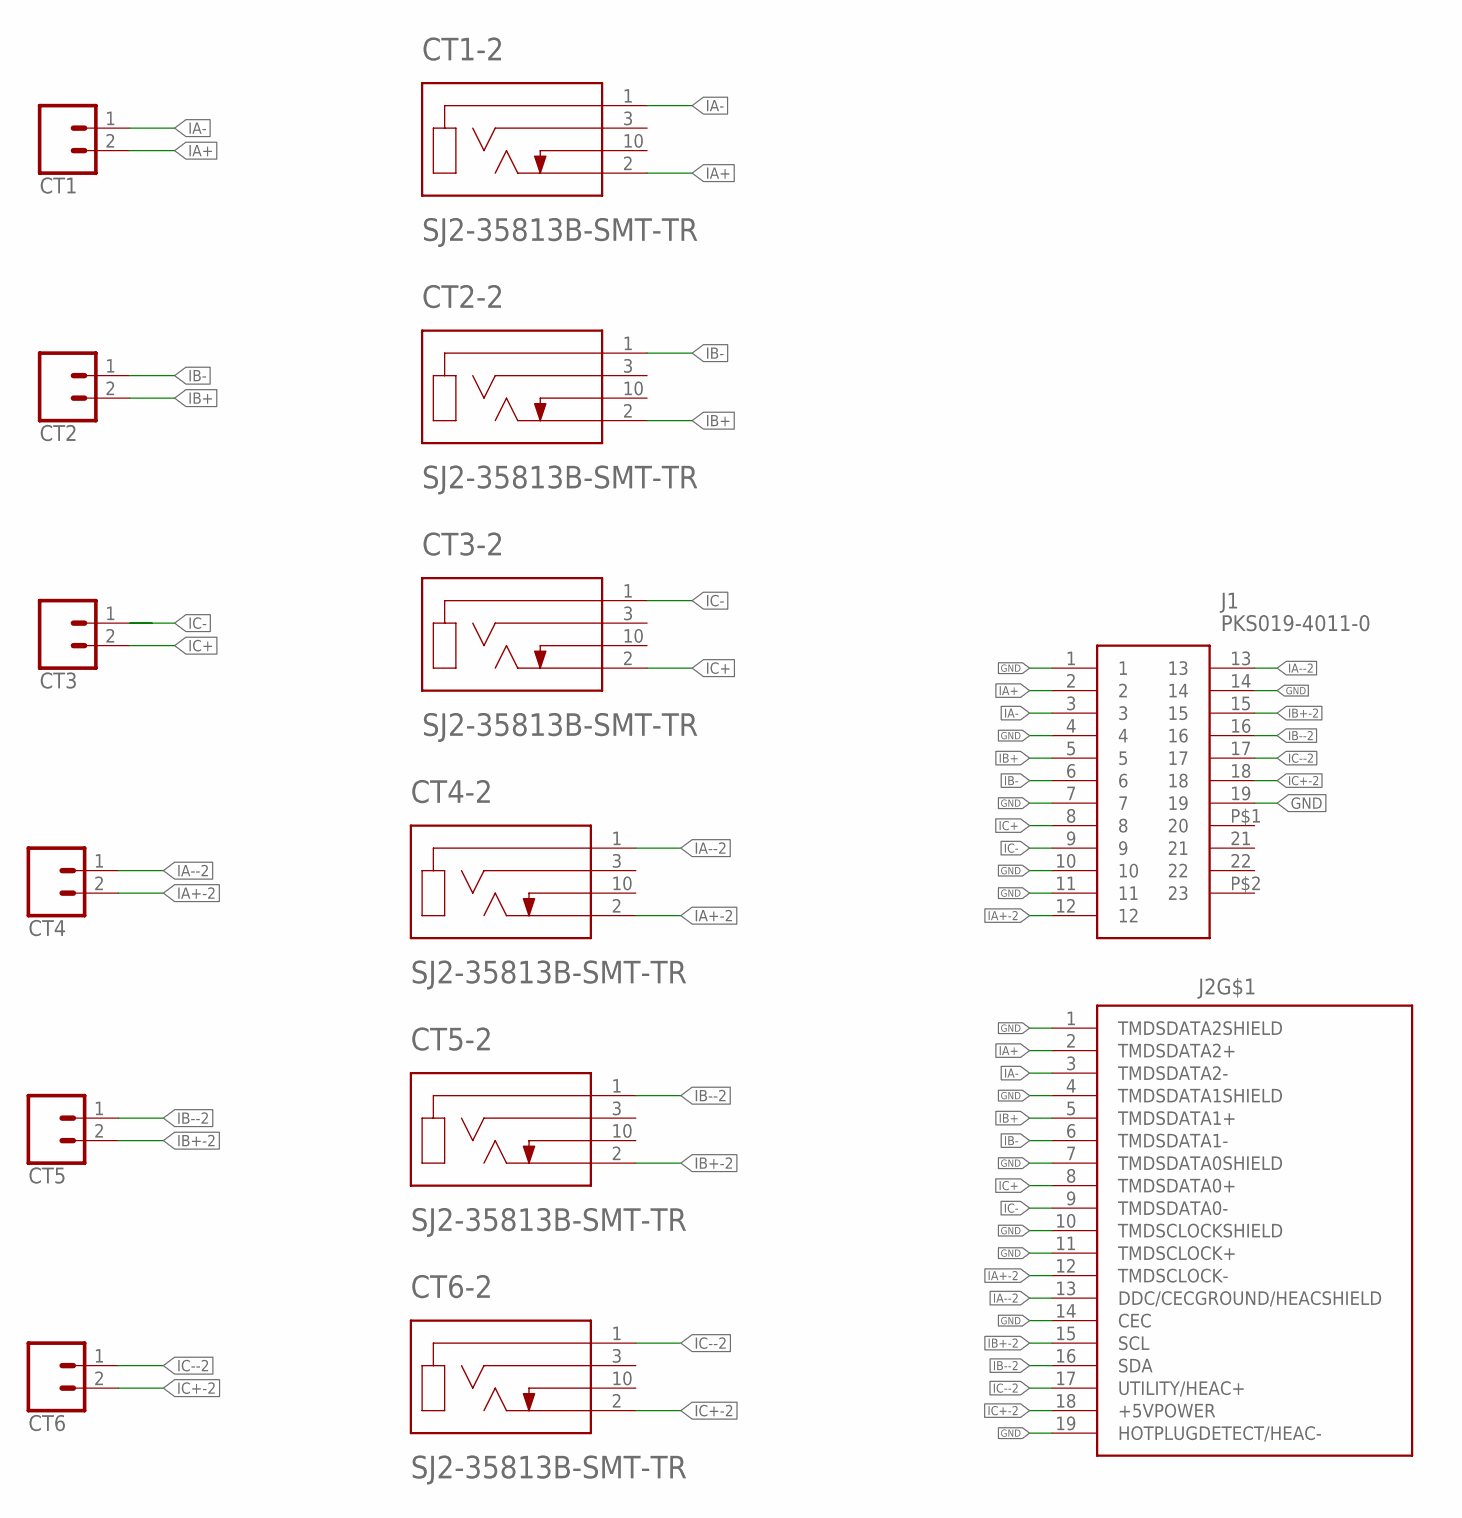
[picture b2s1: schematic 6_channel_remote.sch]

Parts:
CT1, CT2, CT3, CT4, CT5, CT6: CONN_023.5MM; SCREWTERMINAL-3.5MM-2
CT1-2, CT2-2, CT3-2, CT4-2, CT5-2, CT6-2: SJ2-35813B-SMT-TR; CUI_SJ2-35813B-SMT-TR
J1: PKS019-4011-0; PKS01940110
J2: 685119136923

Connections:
GND: J1.1, J1.4, J1.7, J1.10, J1.11, J1.14, J1.19, J2.1 (TMDSDATA2SHIELD), J2.4 (TMDSDATA1SHIELD), J2.7 (TMDSDATA0SHIELD), J2.10 (TMDSCLOCKSHIELD), J2.11 (TMDSCLOCK+), J2.14 (CEC), J2.19 (HOTPLUGDETECT/HEAC-)
IA+: CT1.2, CT1-2.2 (TIP), J1.2, J2.2 (TMDSDATA2+)
IA+-2: CT4.2, CT4-2.2 (TIP), J1.12, J2.12 (TMDSCLOCK-)
IA-: CT1.1, CT1-2.1 (SLEEVE), J1.3, J2.3 (TMDSDATA2-)
IA--2: CT4.1, CT4-2.1 (SLEEVE), J1.13, J2.13 (DDC/CECGROUND/HEACSHIELD)
IB+: CT2.2, CT2-2.2 (TIP), J1.5, J2.5 (TMDSDATA1+)
IB+-2: CT5.2, CT5-2.2 (TIP), J1.15, J2.15 (SCL)
IB-: CT2.1, CT2-2.1 (SLEEVE), J1.6, J2.6 (TMDSDATA1-)
IB--2: CT5.1, CT5-2.1 (SLEEVE), J1.16, J2.16 (SDA)
IC+: CT3.2, CT3-2.2 (TIP), J1.8, J2.8 (TMDSDATA0+)
IC+-2: CT6.2, CT6-2.2 (TIP), J1.18, J2.18 (+5VPOWER)
IC-: CT3.1, CT3-2.1 (SLEEVE), J1.9, J2.9 (TMDSDATA0-)
IC--2: CT6.1, CT6-2.1 (SLEEVE), J1.17, J2.17 (UTILITY/HEAC+)

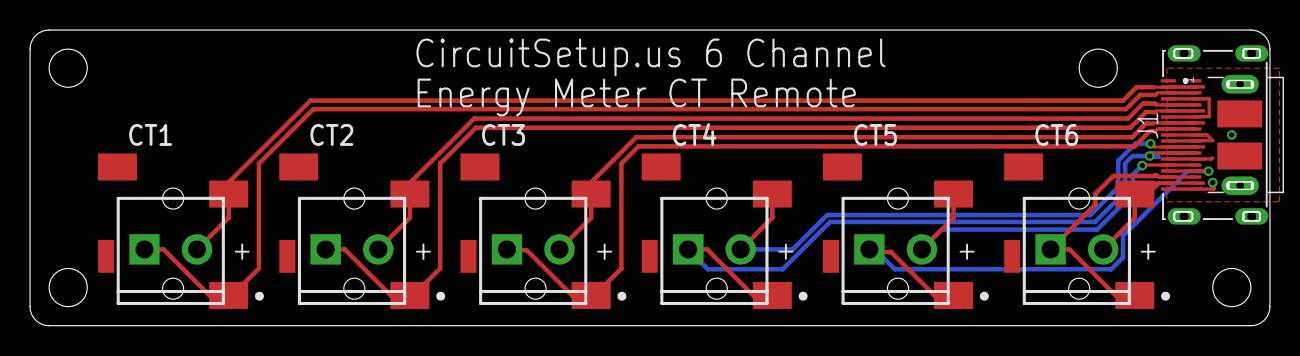
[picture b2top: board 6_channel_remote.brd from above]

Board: 2 copper layers, 82.5 x 19.7 mm, 14 parts (0 on the bottom side), 13 nets.

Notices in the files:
parts and their libraries:
SparkFun-Connectors: Licensing: Creative Commons ShareAlike 4.0 International - https://creativecommons.org/licenses/by-sa/4.0
Wurth_Elektronik_Electromechanic_Input-O: Copyright: Würth Elektronik
